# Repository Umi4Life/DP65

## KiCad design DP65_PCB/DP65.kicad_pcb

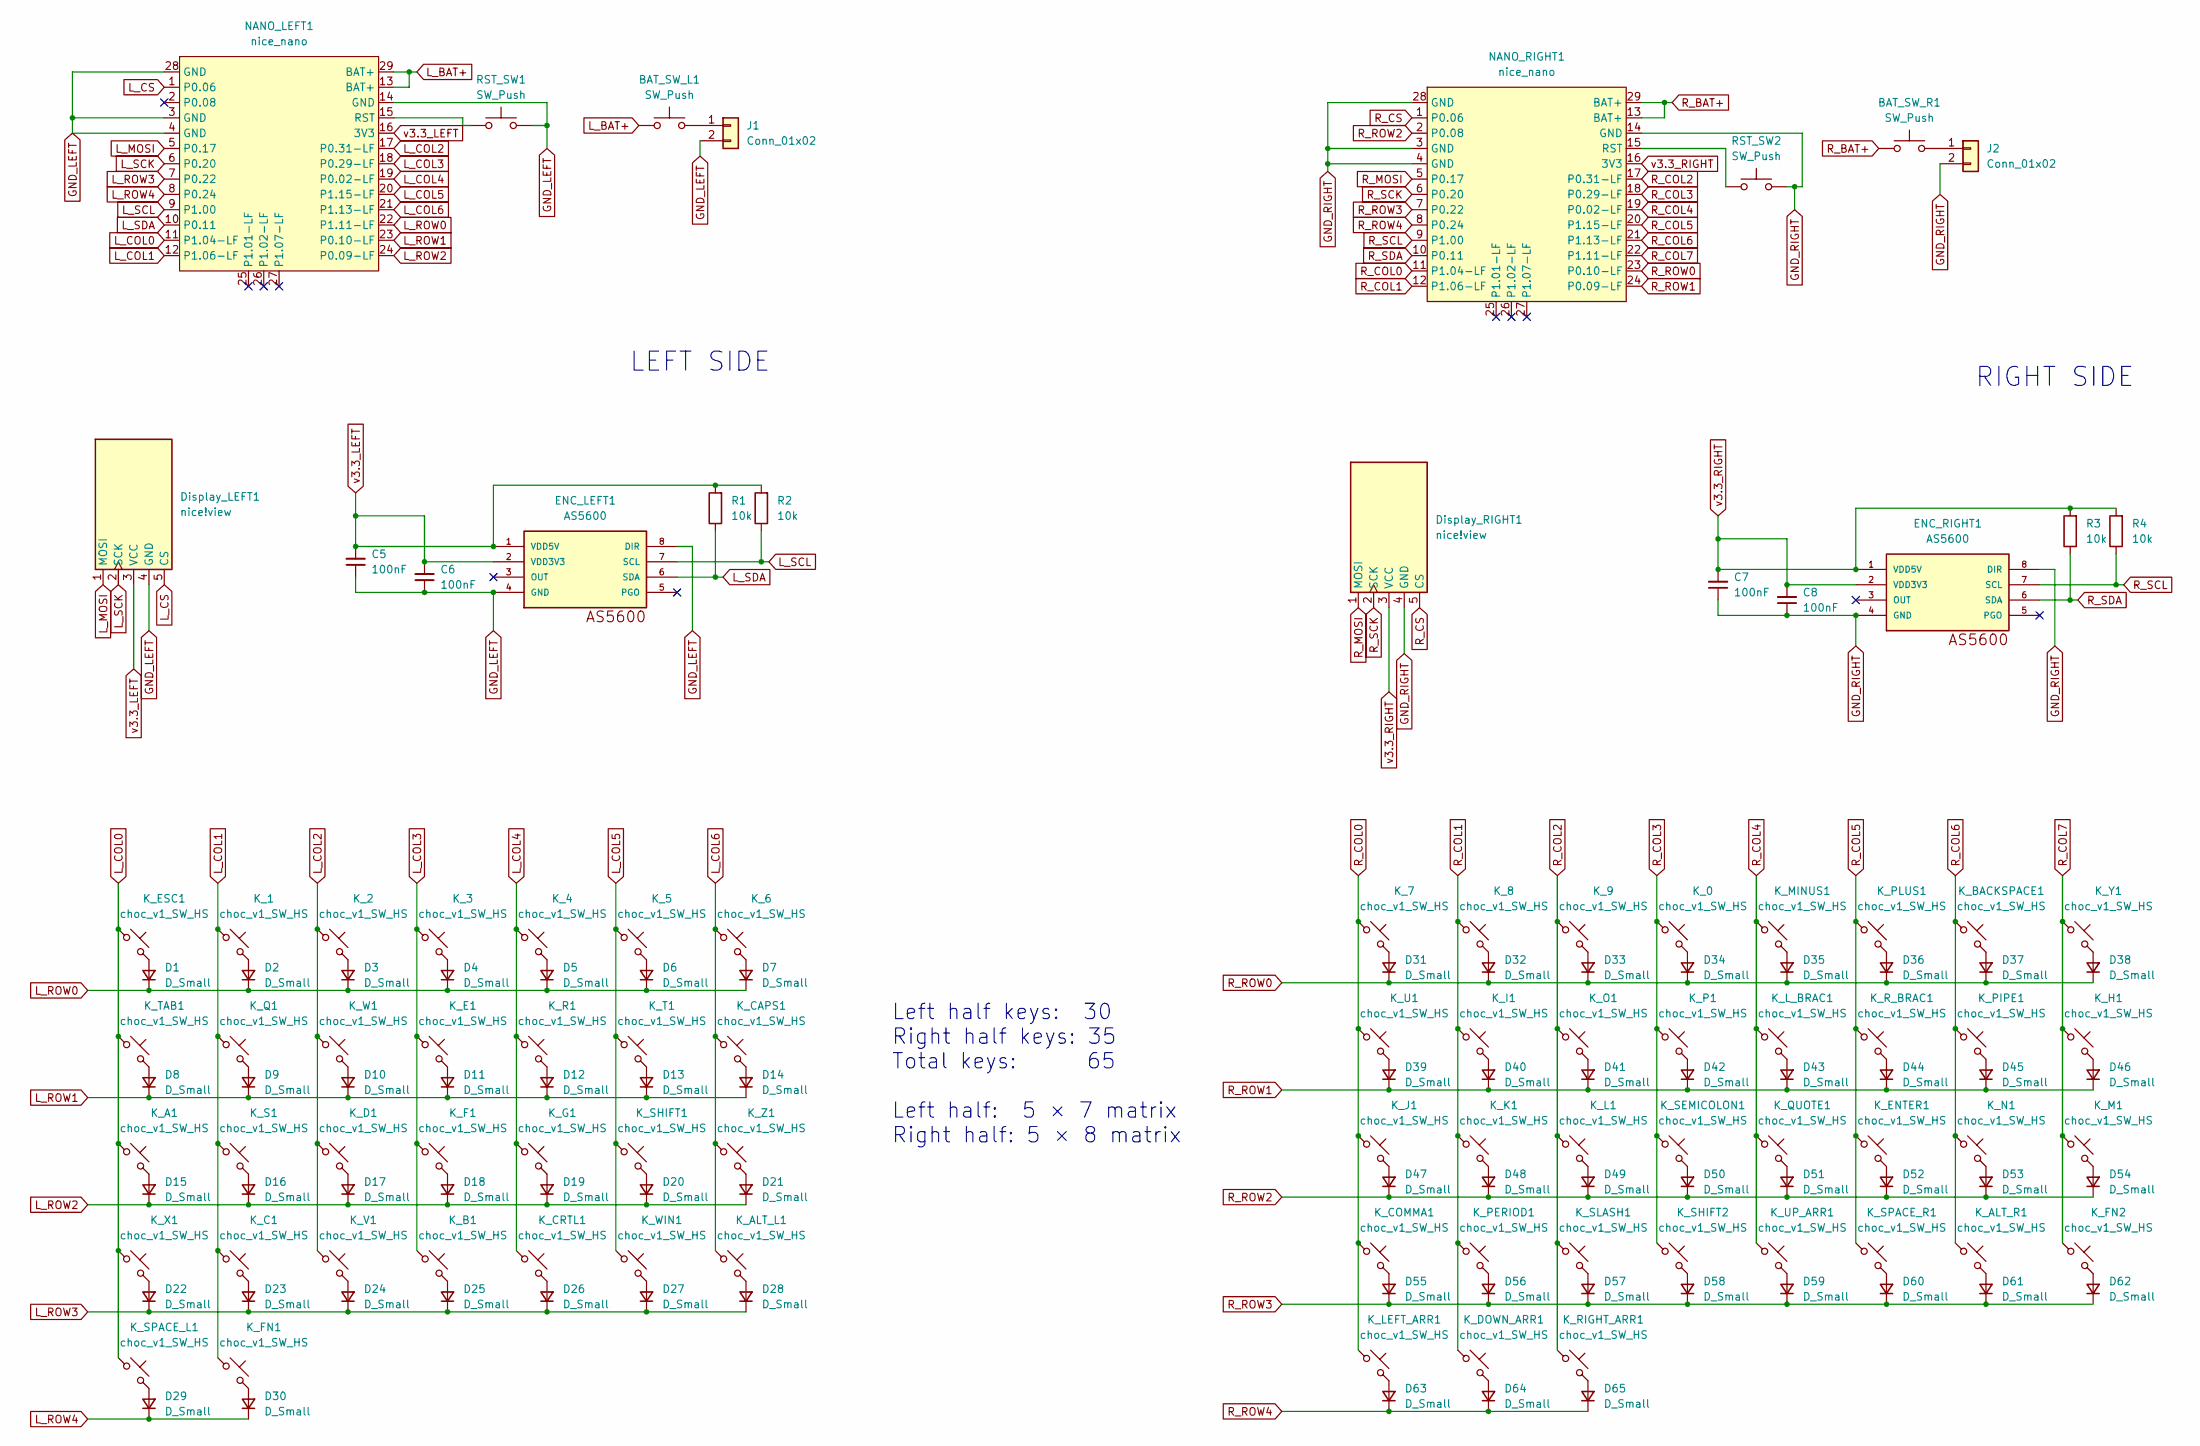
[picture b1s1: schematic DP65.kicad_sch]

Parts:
BAT_SW_L1: SW_Push; SW_Slide_SPDT_Angled_CK_OS102011MA1Q; LCSC C221530
BAT_SW_R1: SW_Push; SW_Slide_SPDT_Angled_CK_OS102011MA1Q; LCSC C221530
C5, C6, C7, C8: 100nF; C_0805_2012Metric_Pad1.18x1.45mm_HandSolder; LCSC C49678
D1, D2, D3, D4, D5, D6, D7, D8, D9, D10, D11, D12, D13, D14, D15, D16, D17, D18, D19, D20, D21, D22, D23, D24, D25, D26, D27, D28, D29, D30, D31, D32, D33, D34, D35, D36, D37, D38, D39, D40, D41, D42, D43, D44, D45, D46, D47, D48, D49, D50, D51, D52, D53, D54, D55, D56, D57, D58, D59, D60, D61, D62, D63, D64, D65: D_Small; D_SOD-123; LCSC C81598
Display_LEFT1: nice!view; PinHeader_1x05_P2.54mm_Vertical
Display_RIGHT1: nice!view; PinHeader_1x05_P2.54mm_Vertical
ENC_LEFT1: AS5600; SOIC8; LCSC C499458
ENC_RIGHT1: AS5600; SOIC8; LCSC C499458
J1, J2: Conn_01x02; JST_PH_S2B-PH-SM4-TB_1x02-1MP_P2.00mm_Horizontal; LCSC C295747
K_0, K_1, K_2, K_3, K_4, K_5, K_6, K_7, K_8, K_9: choc_v1_SW_HS; SW_Hotswap_Kailh_Choc_V1V2_1.00u; LCSC C5333465
K_A1: choc_v1_SW_HS; SW_Hotswap_Kailh_Choc_V1V2_1.00u; LCSC C5333465
K_ALT_L1: choc_v1_SW_HS; SW_Hotswap_Kailh_Choc_V1V2_1.25u; LCSC C5333465
K_ALT_R1: choc_v1_SW_HS; SW_Hotswap_Kailh_Choc_V1V2_1.25u; LCSC C5333465
K_B1: choc_v1_SW_HS; SW_Hotswap_Kailh_Choc_V1V2_1.00u; LCSC C5333465
K_BACKSPACE1: choc_v1_SW_HS; SW_Hotswap_Kailh_Choc_V1V2_2.00u; LCSC C5333465
K_C1: choc_v1_SW_HS; SW_Hotswap_Kailh_Choc_V1V2_1.00u; LCSC C5333465
K_CAPS1: choc_v1_SW_HS; SW_Hotswap_Kailh_Choc_V1V2_1.75u; LCSC C5333465
K_COMMA1: choc_v1_SW_HS; SW_Hotswap_Kailh_Choc_V1V2_1.00u; LCSC C5333465
K_CRTL1: choc_v1_SW_HS; SW_Hotswap_Kailh_Choc_V1V2_1.25u; LCSC C5333465
K_D1: choc_v1_SW_HS; SW_Hotswap_Kailh_Choc_V1V2_1.00u; LCSC C5333465
K_DOWN_ARR1: choc_v1_SW_HS; SW_Hotswap_Kailh_Choc_V1V2_1.00u; LCSC C5333465
K_E1: choc_v1_SW_HS; SW_Hotswap_Kailh_Choc_V1V2_1.00u; LCSC C5333465
K_ENTER1: choc_v1_SW_HS; SW_Hotswap_Kailh_Choc_V1V2_2.25u; LCSC C5333465
K_ESC1: choc_v1_SW_HS; SW_Hotswap_Kailh_Choc_V1V2_1.00u; LCSC C5333465
K_F1: choc_v1_SW_HS; SW_Hotswap_Kailh_Choc_V1V2_1.00u; LCSC C5333465
K_FN1, K_FN2: choc_v1_SW_HS; SW_Hotswap_Kailh_Choc_V1V2_1.25u; LCSC C5333465
K_G1: choc_v1_SW_HS; SW_Hotswap_Kailh_Choc_V1V2_1.00u; LCSC C5333465
K_H1: choc_v1_SW_HS; SW_Hotswap_Kailh_Choc_V1V2_1.00u; LCSC C5333465
K_I1: choc_v1_SW_HS; SW_Hotswap_Kailh_Choc_V1V2_1.00u; LCSC C5333465
K_J1: choc_v1_SW_HS; SW_Hotswap_Kailh_Choc_V1V2_1.00u; LCSC C5333465
K_K1: choc_v1_SW_HS; SW_Hotswap_Kailh_Choc_V1V2_1.00u; LCSC C5333465
K_L1: choc_v1_SW_HS; SW_Hotswap_Kailh_Choc_V1V2_1.00u; LCSC C5333465
K_LEFT_ARR1: choc_v1_SW_HS; SW_Hotswap_Kailh_Choc_V1V2_1.00u; LCSC C5333465
K_L_BRAC1: choc_v1_SW_HS; SW_Hotswap_Kailh_Choc_V1V2_1.00u; LCSC C5333465
K_M1: choc_v1_SW_HS; SW_Hotswap_Kailh_Choc_V1V2_1.00u; LCSC C5333465
K_MINUS1: choc_v1_SW_HS; SW_Hotswap_Kailh_Choc_V1V2_1.00u; LCSC C5333465
K_N1: choc_v1_SW_HS; SW_Hotswap_Kailh_Choc_V1V2_1.00u; LCSC C5333465
K_O1: choc_v1_SW_HS; SW_Hotswap_Kailh_Choc_V1V2_1.00u; LCSC C5333465
K_P1: choc_v1_SW_HS; SW_Hotswap_Kailh_Choc_V1V2_1.00u; LCSC C5333465
K_PERIOD1: choc_v1_SW_HS; SW_Hotswap_Kailh_Choc_V1V2_1.00u; LCSC C5333465
K_PIPE1: choc_v1_SW_HS; SW_Hotswap_Kailh_Choc_V1V2_1.50u; LCSC C5333465
K_PLUS1: choc_v1_SW_HS; SW_Hotswap_Kailh_Choc_V1V2_1.00u; LCSC C5333465
K_Q1: choc_v1_SW_HS; SW_Hotswap_Kailh_Choc_V1V2_1.00u; LCSC C5333465
K_QUOTE1: choc_v1_SW_HS; SW_Hotswap_Kailh_Choc_V1V2_1.00u; LCSC C5333465
K_R1: choc_v1_SW_HS; SW_Hotswap_Kailh_Choc_V1V2_1.00u; LCSC C5333465
K_RIGHT_ARR1: choc_v1_SW_HS; SW_Hotswap_Kailh_Choc_V1V2_1.00u; LCSC C5333465
K_R_BRAC1: choc_v1_SW_HS; SW_Hotswap_Kailh_Choc_V1V2_1.00u; LCSC C5333465
K_S1: choc_v1_SW_HS; SW_Hotswap_Kailh_Choc_V1V2_1.00u; LCSC C5333465
K_SEMICOLON1: choc_v1_SW_HS; SW_Hotswap_Kailh_Choc_V1V2_1.00u; LCSC C5333465
K_SHIFT1: choc_v1_SW_HS; SW_Hotswap_Kailh_Choc_V1V2_2.25u; LCSC C5333465
K_SHIFT2: choc_v1_SW_HS; SW_Hotswap_Kailh_Choc_V1V2_1.75u; LCSC C5333465
K_SLASH1: choc_v1_SW_HS; SW_Hotswap_Kailh_Choc_V1V2_1.00u; LCSC C5333465
K_SPACE_L1: choc_v1_SW_HS; SW_Hotswap_Kailh_Choc_V1V2_2.25u; LCSC C5333465
K_SPACE_R1: choc_v1_SW_HS; SW_Hotswap_Kailh_Choc_V1V2_2.25u; LCSC C5333465
K_T1: choc_v1_SW_HS; SW_Hotswap_Kailh_Choc_V1V2_1.00u; LCSC C5333465
K_TAB1: choc_v1_SW_HS; SW_Hotswap_Kailh_Choc_V1V2_1.50u; LCSC C5333465
K_U1: choc_v1_SW_HS; SW_Hotswap_Kailh_Choc_V1V2_1.00u; LCSC C5333465
K_UP_ARR1: choc_v1_SW_HS; SW_Hotswap_Kailh_Choc_V1V2_1.00u; LCSC C5333465
K_V1: choc_v1_SW_HS; SW_Hotswap_Kailh_Choc_V1V2_1.00u; LCSC C5333465
K_W1: choc_v1_SW_HS; SW_Hotswap_Kailh_Choc_V1V2_1.00u; LCSC C5333465
K_WIN1: choc_v1_SW_HS; SW_Hotswap_Kailh_Choc_V1V2_1.25u; LCSC C5333465
K_X1: choc_v1_SW_HS; SW_Hotswap_Kailh_Choc_V1V2_1.00u; LCSC C5333465
K_Y1: choc_v1_SW_HS; SW_Hotswap_Kailh_Choc_V1V2_1.00u; LCSC C5333465
K_Z1: choc_v1_SW_HS; SW_Hotswap_Kailh_Choc_V1V2_1.00u; LCSC C5333465
NANO_LEFT1: nice_nano; nice_nano_AH_USBup
NANO_RIGHT1: nice_nano; nice_nano_AH_USBup
R1, R2, R3, R4: 10k; R_0805_2012Metric; LCSC C17414
RST_SW1, RST_SW2: SW_Push; SW_Tactile_SKHH_Angled; LCSC C383800

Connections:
GND_LEFT: C5.1, C6.1, Display_LEFT1.4 (GND), ENC_LEFT1.4 (GND), ENC_LEFT1.8 (DIR), J1.2, NANO_LEFT1.3 (GND), NANO_LEFT1.4 (GND), NANO_LEFT1.14 (GND), NANO_LEFT1.28 (GND), RST_SW1.2
GND_RIGHT: C7.1, C8.1, Display_RIGHT1.4 (GND), ENC_RIGHT1.4 (GND), ENC_RIGHT1.8 (DIR), J2.2, NANO_RIGHT1.3 (GND), NANO_RIGHT1.4 (GND), NANO_RIGHT1.14 (GND), NANO_RIGHT1.28 (GND), RST_SW2.2
L_BAT+: BAT_SW_L1.1, NANO_LEFT1.13 (BAT+), NANO_LEFT1.29 (BAT+)
L_COL0: K_A1.1, K_ESC1.1, K_SPACE_L1.1, K_TAB1.1, K_X1.1, NANO_LEFT1.11 (P1.04-LF)
L_COL1: K_1.1, K_C1.1, K_FN1.1, K_Q1.1, K_S1.1, NANO_LEFT1.12 (P1.06-LF)
L_COL2: K_2.1, K_D1.1, K_V1.1, K_W1.1, NANO_LEFT1.17 (P0.31-LF)
L_COL3: K_3.1, K_B1.1, K_E1.1, K_F1.1, NANO_LEFT1.18 (P0.29-LF)
L_COL4: K_4.1, K_CRTL1.1, K_G1.1, K_R1.1, NANO_LEFT1.19 (P0.02-LF)
L_COL5: K_5.1, K_SHIFT1.1, K_T1.1, K_WIN1.1, NANO_LEFT1.20 (P1.15-LF)
L_COL6: K_6.1, K_ALT_L1.1, K_CAPS1.1, K_Z1.1, NANO_LEFT1.21 (P1.13-LF)
L_CS: Display_LEFT1.5 (CS), NANO_LEFT1.1 (P0.06)
L_MOSI: Display_LEFT1.1 (MOSI), NANO_LEFT1.5 (P0.17)
L_ROW0: D1.1 (K), D2.1 (K), D3.1 (K), D4.1 (K), D5.1 (K), D6.1 (K), D7.1 (K), NANO_LEFT1.22 (P1.11-LF)
L_ROW1: D8.1 (K), D9.1 (K), D10.1 (K), D11.1 (K), D12.1 (K), D13.1 (K), D14.1 (K), NANO_LEFT1.23 (P0.10-LF)
L_ROW2: D15.1 (K), D16.1 (K), D17.1 (K), D18.1 (K), D19.1 (K), D20.1 (K), D21.1 (K), NANO_LEFT1.24 (P0.09-LF)
L_ROW3: D22.1 (K), D23.1 (K), D24.1 (K), D25.1 (K), D26.1 (K), D27.1 (K), D28.1 (K), NANO_LEFT1.7 (P0.22)
L_ROW4: D29.1 (K), D30.1 (K), NANO_LEFT1.8 (P0.24)
L_SCK: Display_LEFT1.2 (SCK), NANO_LEFT1.6 (P0.20)
L_SCL: ENC_LEFT1.7 (SCL), NANO_LEFT1.9 (P1.00), R2.1
L_SDA: ENC_LEFT1.6 (SDA), NANO_LEFT1.10 (P0.11), R1.1
unnamed: D1.2 (A), K_ESC1.2
unnamed: D2.2 (A), K_1.2
unnamed: D3.2 (A), K_2.2
unnamed: D4.2 (A), K_3.2
unnamed: D5.2 (A), K_4.2
unnamed: D6.2 (A), K_5.2
unnamed: D7.2 (A), K_6.2
unnamed: D8.2 (A), K_TAB1.2
unnamed: D9.2 (A), K_Q1.2
unnamed: D10.2 (A), K_W1.2
unnamed: D11.2 (A), K_E1.2
unnamed: D12.2 (A), K_R1.2
unnamed: D13.2 (A), K_T1.2
unnamed: D14.2 (A), K_CAPS1.2
unnamed: D15.2 (A), K_A1.2
unnamed: D16.2 (A), K_S1.2
unnamed: D17.2 (A), K_D1.2
unnamed: D18.2 (A), K_F1.2
unnamed: D19.2 (A), K_G1.2
unnamed: D20.2 (A), K_SHIFT1.2
unnamed: D21.2 (A), K_Z1.2
unnamed: D22.2 (A), K_X1.2
unnamed: D23.2 (A), K_C1.2
unnamed: D24.2 (A), K_V1.2
unnamed: D25.2 (A), K_B1.2
unnamed: D26.2 (A), K_CRTL1.2
unnamed: D27.2 (A), K_WIN1.2
unnamed: D28.2 (A), K_ALT_L1.2
unnamed: D29.2 (A), K_SPACE_L1.2
unnamed: D30.2 (A), K_FN1.2
unnamed: D31.2 (A), K_7.2
unnamed: D32.2 (A), K_8.2
unnamed: D33.2 (A), K_9.2
unnamed: D34.2 (A), K_0.2
unnamed: D35.2 (A), K_MINUS1.2
unnamed: D36.2 (A), K_PLUS1.2
unnamed: D37.2 (A), K_BACKSPACE1.2
unnamed: D38.2 (A), K_Y1.2
unnamed: D39.2 (A), K_U1.2
unnamed: D40.2 (A), K_I1.2
unnamed: D41.2 (A), K_O1.2
unnamed: D42.2 (A), K_P1.2
unnamed: D43.2 (A), K_L_BRAC1.2
unnamed: D44.2 (A), K_R_BRAC1.2
unnamed: D45.2 (A), K_PIPE1.2
unnamed: D46.2 (A), K_H1.2
unnamed: D47.2 (A), K_J1.2
unnamed: D48.2 (A), K_K1.2
unnamed: D49.2 (A), K_L1.2
unnamed: D50.2 (A), K_SEMICOLON1.2
unnamed: D51.2 (A), K_QUOTE1.2
unnamed: D52.2 (A), K_ENTER1.2
unnamed: D53.2 (A), K_N1.2
unnamed: D54.2 (A), K_M1.2
unnamed: D55.2 (A), K_COMMA1.2
unnamed: D56.2 (A), K_PERIOD1.2
unnamed: D57.2 (A), K_SLASH1.2
unnamed: D58.2 (A), K_SHIFT2.2
unnamed: D59.2 (A), K_UP_ARR1.2
unnamed: D60.2 (A), K_SPACE_R1.2
unnamed: D61.2 (A), K_ALT_R1.2
unnamed: D62.2 (A), K_FN2.2
unnamed: D63.2 (A), K_LEFT_ARR1.2
unnamed: D64.2 (A), K_DOWN_ARR1.2
unnamed: D65.2 (A), K_RIGHT_ARR1.2
unnamed: BAT_SW_L1.2, J1.1
unnamed: BAT_SW_R1.2, J2.1
unnamed: NANO_LEFT1.15 (RST), RST_SW1.1
unnamed: NANO_RIGHT1.15 (RST), RST_SW2.1
R_BAT+: BAT_SW_R1.1, NANO_RIGHT1.13 (BAT+), NANO_RIGHT1.29 (BAT+)
R_COL0: K_7.1, K_COMMA1.1, K_J1.1, K_LEFT_ARR1.1, K_U1.1, NANO_RIGHT1.11 (P1.04-LF)
R_COL1: K_8.1, K_DOWN_ARR1.1, K_I1.1, K_K1.1, K_PERIOD1.1, NANO_RIGHT1.12 (P1.06-LF)
R_COL2: K_9.1, K_L1.1, K_O1.1, K_RIGHT_ARR1.1, K_SLASH1.1, NANO_RIGHT1.17 (P0.31-LF)
R_COL3: K_0.1, K_P1.1, K_SEMICOLON1.1, K_SHIFT2.1, NANO_RIGHT1.18 (P0.29-LF)
R_COL4: K_L_BRAC1.1, K_MINUS1.1, K_QUOTE1.1, K_UP_ARR1.1, NANO_RIGHT1.19 (P0.02-LF)
R_COL5: K_ENTER1.1, K_PLUS1.1, K_R_BRAC1.1, K_SPACE_R1.1, NANO_RIGHT1.20 (P1.15-LF)
R_COL6: K_ALT_R1.1, K_BACKSPACE1.1, K_N1.1, K_PIPE1.1, NANO_RIGHT1.21 (P1.13-LF)
R_COL7: K_FN2.1, K_H1.1, K_M1.1, K_Y1.1, NANO_RIGHT1.22 (P1.11-LF)
R_CS: Display_RIGHT1.5 (CS), NANO_RIGHT1.1 (P0.06)
R_MOSI: Display_RIGHT1.1 (MOSI), NANO_RIGHT1.5 (P0.17)
R_ROW0: D31.1 (K), D32.1 (K), D33.1 (K), D34.1 (K), D35.1 (K), D36.1 (K), D37.1 (K), D38.1 (K), NANO_RIGHT1.23 (P0.10-LF)
R_ROW1: D39.1 (K), D40.1 (K), D41.1 (K), D42.1 (K), D43.1 (K), D44.1 (K), D45.1 (K), D46.1 (K), NANO_RIGHT1.24 (P0.09-LF)
R_ROW2: D47.1 (K), D48.1 (K), D49.1 (K), D50.1 (K), D51.1 (K), D52.1 (K), D53.1 (K), D54.1 (K), NANO_RIGHT1.2 (P0.08)
R_ROW3: D55.1 (K), D56.1 (K), D57.1 (K), D58.1 (K), D59.1 (K), D60.1 (K), D61.1 (K), D62.1 (K), NANO_RIGHT1.7 (P0.22)
R_ROW4: D63.1 (K), D64.1 (K), D65.1 (K), NANO_RIGHT1.8 (P0.24)
R_SCK: Display_RIGHT1.2 (SCK), NANO_RIGHT1.6 (P0.20)
R_SCL: ENC_RIGHT1.7 (SCL), NANO_RIGHT1.9 (P1.00), R4.1
R_SDA: ENC_RIGHT1.6 (SDA), NANO_RIGHT1.10 (P0.11), R3.1
v3.3_LEFT: C5.2, C6.2, Display_LEFT1.3 (VCC), ENC_LEFT1.1 (VDD5V), ENC_LEFT1.2 (VDD3V3), NANO_LEFT1.16 (3V3), R1.2, R2.2
v3.3_RIGHT: C7.2, C8.2, Display_RIGHT1.3 (VCC), ENC_RIGHT1.1 (VDD5V), ENC_RIGHT1.2 (VDD3V3), NANO_RIGHT1.16 (3V3), R3.2, R4.2

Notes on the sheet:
RIGHT SIDE
Left half keys: 30 Right half keys: 35 Total keys: 65 Left half: 5 × 7 matrix Right half: 5 × 8 matrix
LEFT SIDE

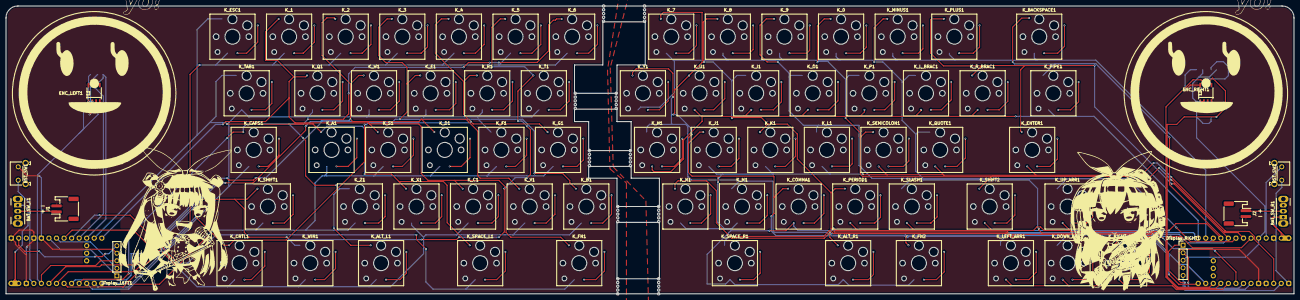
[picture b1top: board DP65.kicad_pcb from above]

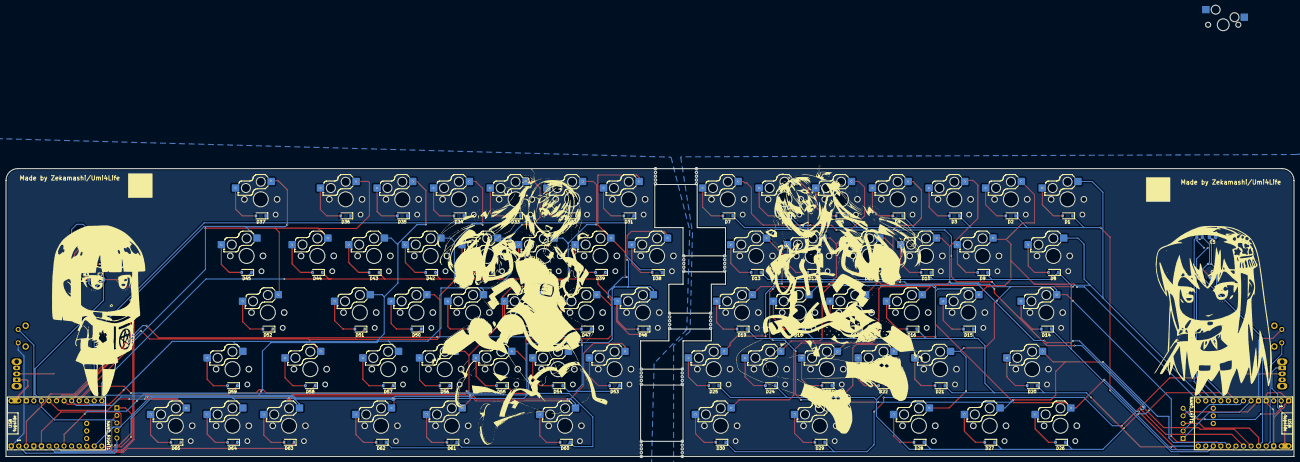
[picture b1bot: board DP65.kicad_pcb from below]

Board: 2 copper layers, 433.4 x 96.8 mm, 150 parts (75 on the bottom side), 110 nets.

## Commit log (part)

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2026-05-14 Add submodules
2026-05-17 schematics
2026-06-02 firmware: add ZMK scaffold for DP65
2026-06-02 ci: fix ZMK west workspace path
